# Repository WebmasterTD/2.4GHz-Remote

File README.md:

# 2.4GHz-Remote

This is an arduino and nRF24L01 based project, the goal is to make a radio controlled plug / relay, with reach > 500 m.
This code is not fully implemented yet and not well commented. It will eventuallly improve with time.

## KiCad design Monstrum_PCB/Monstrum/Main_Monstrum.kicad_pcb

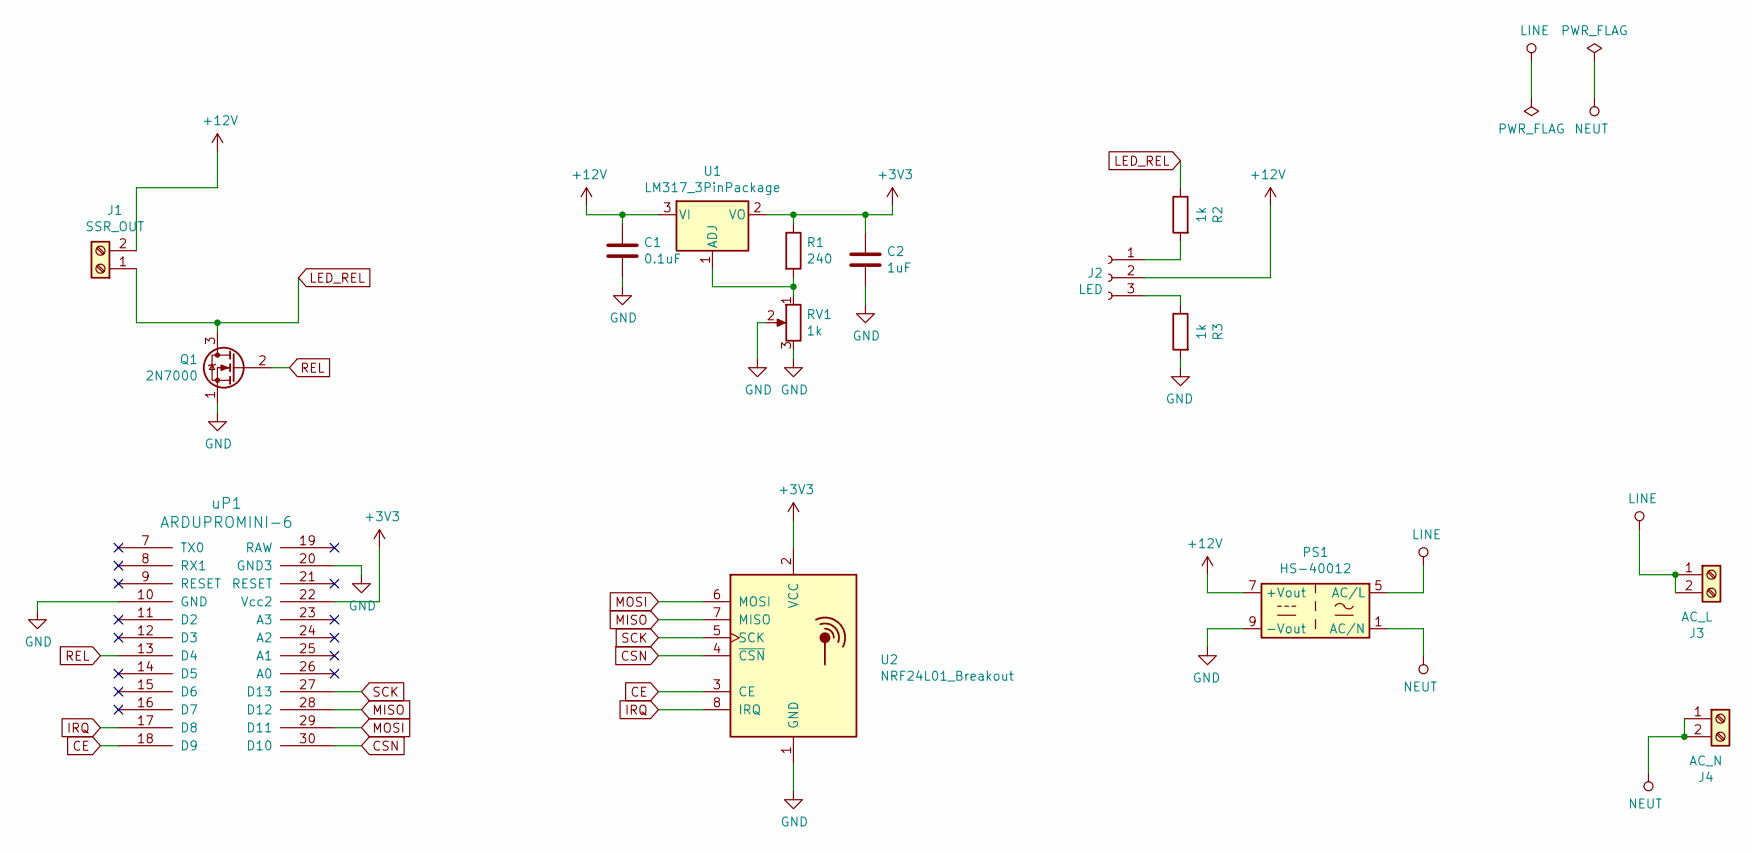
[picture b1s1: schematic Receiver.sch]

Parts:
C1: 0.1uF; C_Disc_D5.0mm_W2.5mm_P2.50mm
C2: 1uF; C_Disc_D4.7mm_W2.5mm_P5.00mm
J1: SSR_OUT; TerminalBlock_RND_205-00012_1x02_P5.00mm_Horizontal
J2: LED; PinHeader_1x03_P2.54mm_Vertical
J3: AC_L; TerminalBlock_RND_205-00012_1x02_P5.00mm_Horizontal
J4: AC_N; TerminalBlock_RND_205-00012_1x02_P5.00mm_Horizontal
PS1: HS-40012; Converter_ACDC_Hahn_HS-400xx_THT
Q1: 2N7000; TO-92L_Inline_Wide
R1: 240; R_Axial_DIN0207_L6.3mm_D2.5mm_P10.16mm_Horizontal
R2, R3: 1k; R_Axial_DIN0207_L6.3mm_D2.5mm_P10.16mm_Horizontal
RV1: 1k; Potentiometer_Vishay_T73XX_Horizontal
U1: LM317_3PinPackage; TO-220-3_Vertical
U2: NRF24L01_Breakout; PinHeader_2x04_P2.54mm_Vertical
uP1: ARDUPROMINI-6; ArduProMini-CUSTOM

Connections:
+3V3: C2.1, R1.1, U1.2 (VO), U2.2 (VCC), uP1.22 (Vcc2)
+12V: C1.1, J1.2, J2.2, PS1.7 (+Vout), U1.3 (VI)
CE: U2.3 (CE), uP1.18 (D9)
CSN: U2.4 (~CSN), uP1.30 (D10)
GND: C1.2, C2.2, PS1.9 (-Vout), Q1.1 (S), R3.2, RV1.2, RV1.3, U2.1 (GND), uP1.10 (GND), uP1.20 (GND3)
IRQ: U2.8 (IRQ), uP1.17 (D8)
LED_REL: J1.1, Q1.3 (D), R2.1
LINE: J3.1, J3.2, PS1.5 (AC/L)
MISO: U2.7 (MISO), uP1.28 (D12)
MOSI: U2.6 (MOSI), uP1.29 (D11)
NEUT: J4.1, J4.2, PS1.1 (AC/N)
unnamed: J2.1, R2.2
unnamed: J2.3, R3.1
unnamed: R1.2, RV1.1, U1.1 (ADJ)
REL: Q1.2 (G), uP1.13 (D4)
SCK: U2.5 (SCK), uP1.27 (D13)

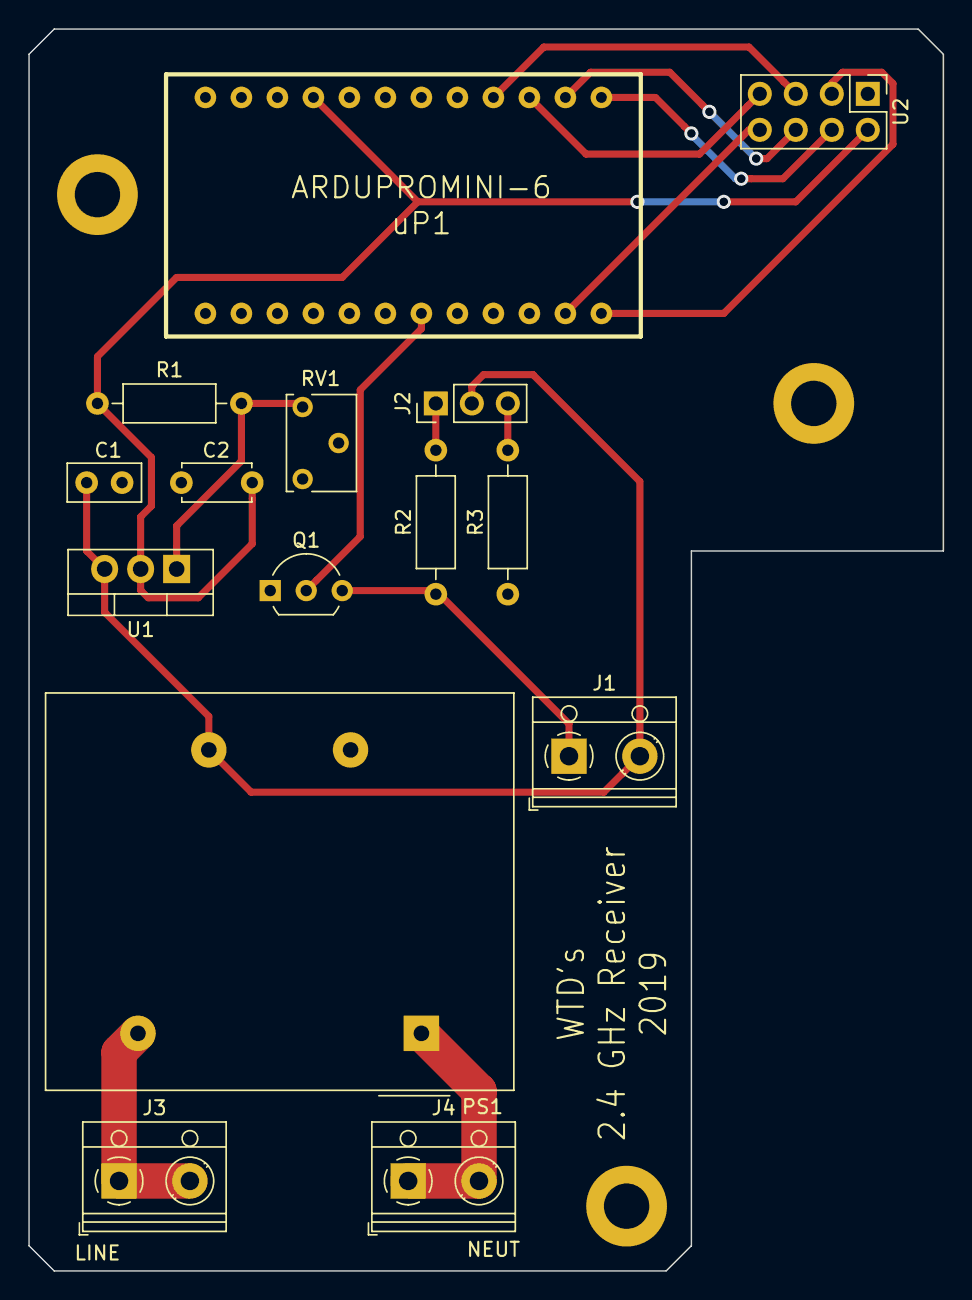
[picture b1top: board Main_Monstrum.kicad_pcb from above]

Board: 2 copper layers, 64.5 x 87.6 mm, 18 parts (0 on the bottom side), 16 nets.

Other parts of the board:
 : MountingHole_3.2mm_M3_ISO7380_Pad
 #2,  #3: MountingHole_3.2mm_M3_ISO7380_Pad

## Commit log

2016-01-12 :neckbeard: Added .gitattributes
2016-01-12 Base code
    1st working version
2016-01-17 Moved_functions_to_header
2016-01-17 Revert "Moved_functions_to_header"
    This reverts commit a1d95abd3557b5f1d81b8474d028c78e0c1f6c4c.
2016-01-17 Moved Functions to header
2016-01-23 powertest
2016-02-14 wake function included
2016-02-14 EN & PS pin debugged
2016-02-14 Power saving update
2016-05-09 added RX mem compare
2016-05-09 compare methods
2016-05-10 Working with relay
2016-05-15 working version
2017-04-01 Relay false startup fixed
2017-04-01 False relay start fixed
2018-10-14 Updated Folder and File names
2018-10-15 Added KiCad project
2018-10-17 Schematic structure created
2018-10-17 updated schematic
2018-10-21 SChematic updates
